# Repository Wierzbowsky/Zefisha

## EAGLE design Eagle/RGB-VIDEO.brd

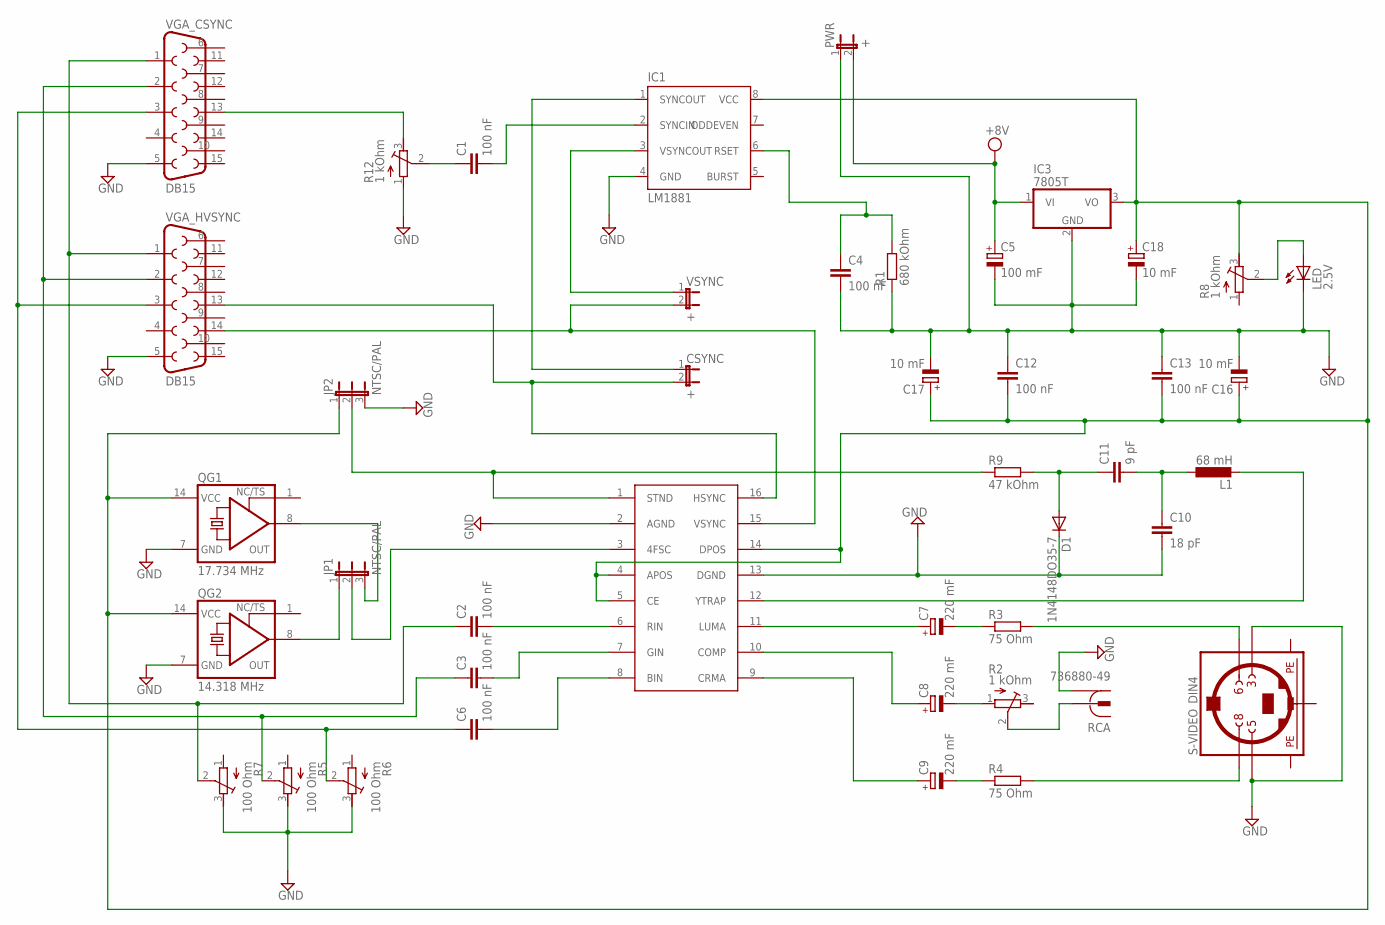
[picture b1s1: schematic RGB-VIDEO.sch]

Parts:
C1, C2, C3, C4, C6, C12, C13: 100 nF; C050-025X075
C5: 100 mF; E3,5-10
C7, C8, C9: 220 mF; E3,5-10
C10: 18 pF; C025-024X044
C11: 9 pF; C025-024X044
C16, C17, C18: 10 mF; E3,5-8
CSYNC: +; JP1
D1: 1N4148DO35-7; DO35-7
IC1: LM1881; DIL08
IC2: AD725; SO16W
IC3: 7805T; TO220H
JP1, JP2: NTSC/PAL; JP2
L1: 68 mH; 6000-XXXX-RC
LED: 2.5V; LED3MM
PWR: +; JP1
QG1: 17.734 MHz; DIL14S
QG2: 14.318 MHz; DIL14S
R1: 680 kOhm; 0204/7
R2, R8, R12: 1 kOhm; RTRIM3339P
R3, R4: 75 Ohm; 0204/7
R5, R6, R7: 100 Ohm; RTRIM3339P
R9: 47 kOhm; 0204/7
RCA: 736880-49
S-VIDEO: DIN4; M_DIN4
VGA_CSYNC: DB15
VGA_HVSYNC: DB15
VSYNC: +; JP1

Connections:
+5V: C12.2, C13.2, C16.+, C17.+, C18.+, IC1.8 (VCC), IC2.4 (APOS), IC2.5 (CE), IC2.14 (DPOS), IC3.3 (VO), JP2.1, QG1.14 (VCC), QG2.14 (VCC), R8.3 (E)
CSYNC: CSYNC.1, IC1.1 (SYNCOUT)
GND: C4.2, C5.-, C10.2, C12.1, C13.1, C16.-, C17.-, C18.-, D1.C, IC1.4 (GND), IC2.2 (AGND), IC2.13 (DGND), IC3.2 (GND), JP2.3, LED.K (C), PWR.1, QG1.7 (GND), QG2.7 (GND), R1.1, R5.3 (E), R6.3 (E), R7.3 (E), R12.1 (A), RCA.1, RCA.1@1 (1), RCA.1@2 (1), S-VIDEO.3, S-VIDEO.5, VGA_CSYNC.5, VGA_HVSYNC.5
HSYNC: CSYNC.2, IC2.16 (HSYNC), VGA_HVSYNC.13
unnamed: C4.1, IC1.6 (RSET), R1.2
unnamed: C1.2, IC1.2 (SYNCIN)
unnamed: LED.A, R8.2 (S)
unnamed: JP1.1, QG2.8 (OUT)
unnamed: JP1.3, QG1.8 (OUT)
unnamed: IC2.3 (4FSC), JP1.2
unnamed: C2.2, IC2.6 (RIN)
unnamed: C3.2, IC2.7 (GIN)
unnamed: C6.2, IC2.8 (BIN)
unnamed: C2.1, R7.2 (S), VGA_CSYNC.1, VGA_HVSYNC.1
unnamed: C3.1, R5.2 (S), VGA_CSYNC.2, VGA_HVSYNC.2
unnamed: C6.1, R6.2 (S), VGA_CSYNC.3, VGA_HVSYNC.3
unnamed: C8.-, R2.1 (A)
unnamed: R2.2 (S), RCA.2
unnamed: C7.-, R3.1
unnamed: R3.2, S-VIDEO.6
unnamed: C7.+, IC2.11 (LUMA)
unnamed: C8.+, IC2.10 (COMP)
unnamed: C9.+, IC2.9 (CRMA)
unnamed: C9.-, R4.1
unnamed: R4.2, S-VIDEO.8
unnamed: C11.1, D1.A, R9.2
unnamed: C10.1, C11.2, L1.1
unnamed: IC2.12 (YTRAP), L1.2
unnamed: IC1.3 (VSYNCOUT), VSYNC.1
unnamed: C1.1, R12.2 (S)
PE1: S-VIDEO.SH1 (PE1)
PE2: S-VIDEO.SH2 (PE2)
PE3: S-VIDEO.SH3 (PE3)
STND: IC2.1 (STND), JP2.2, R9.1
VCC: C5.+, IC3.1 (VI), PWR.2
VGA_CSYNC: R12.3 (E), VGA_CSYNC.13
VSYNC: IC2.15 (VSYNC), VGA_HVSYNC.14, VSYNC.2

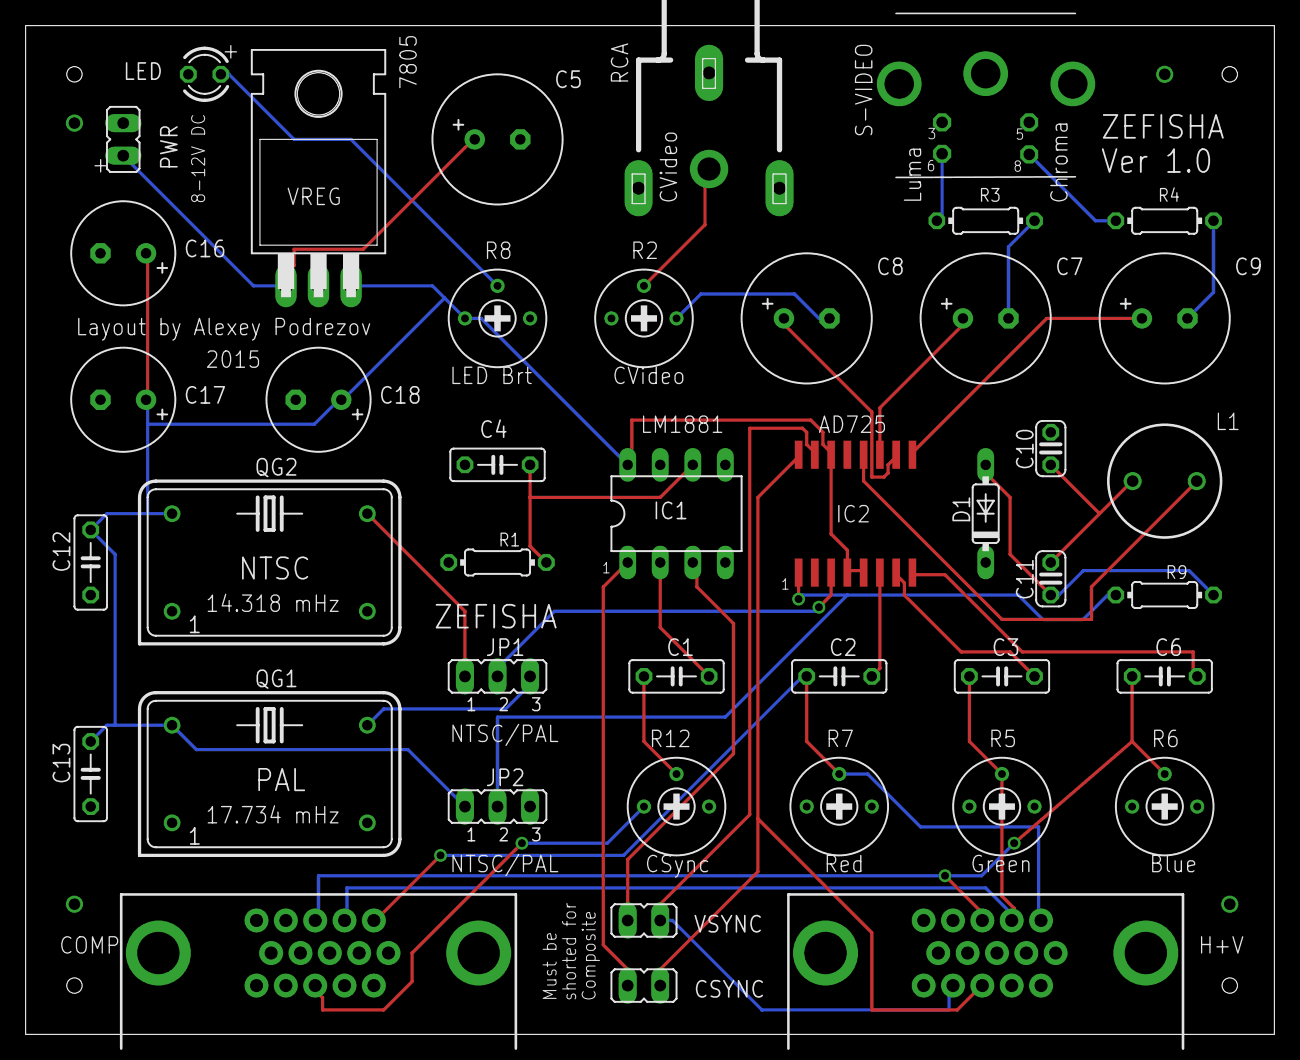
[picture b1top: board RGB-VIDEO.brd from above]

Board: 2 copper layers, 97.5 x 78.7 mm, 43 parts (0 on the bottom side), 34 nets.

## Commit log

2015-12-30 :neckbeard: Added .gitattributes & .gitignore files
2015-12-30 First version of the controller
    First version of the controller, tested, accepted for production.
2016-01-26 Added board file, removed pro file
2016-05-27 Partslist
2017-05-20 Renamed board's folder

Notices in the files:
parts and their libraries:
SparkFun-Connectors: Licensing: Creative Commons ShareAlike 4.0 International - https://creativecommons.org/licenses/by-sa/4.0
